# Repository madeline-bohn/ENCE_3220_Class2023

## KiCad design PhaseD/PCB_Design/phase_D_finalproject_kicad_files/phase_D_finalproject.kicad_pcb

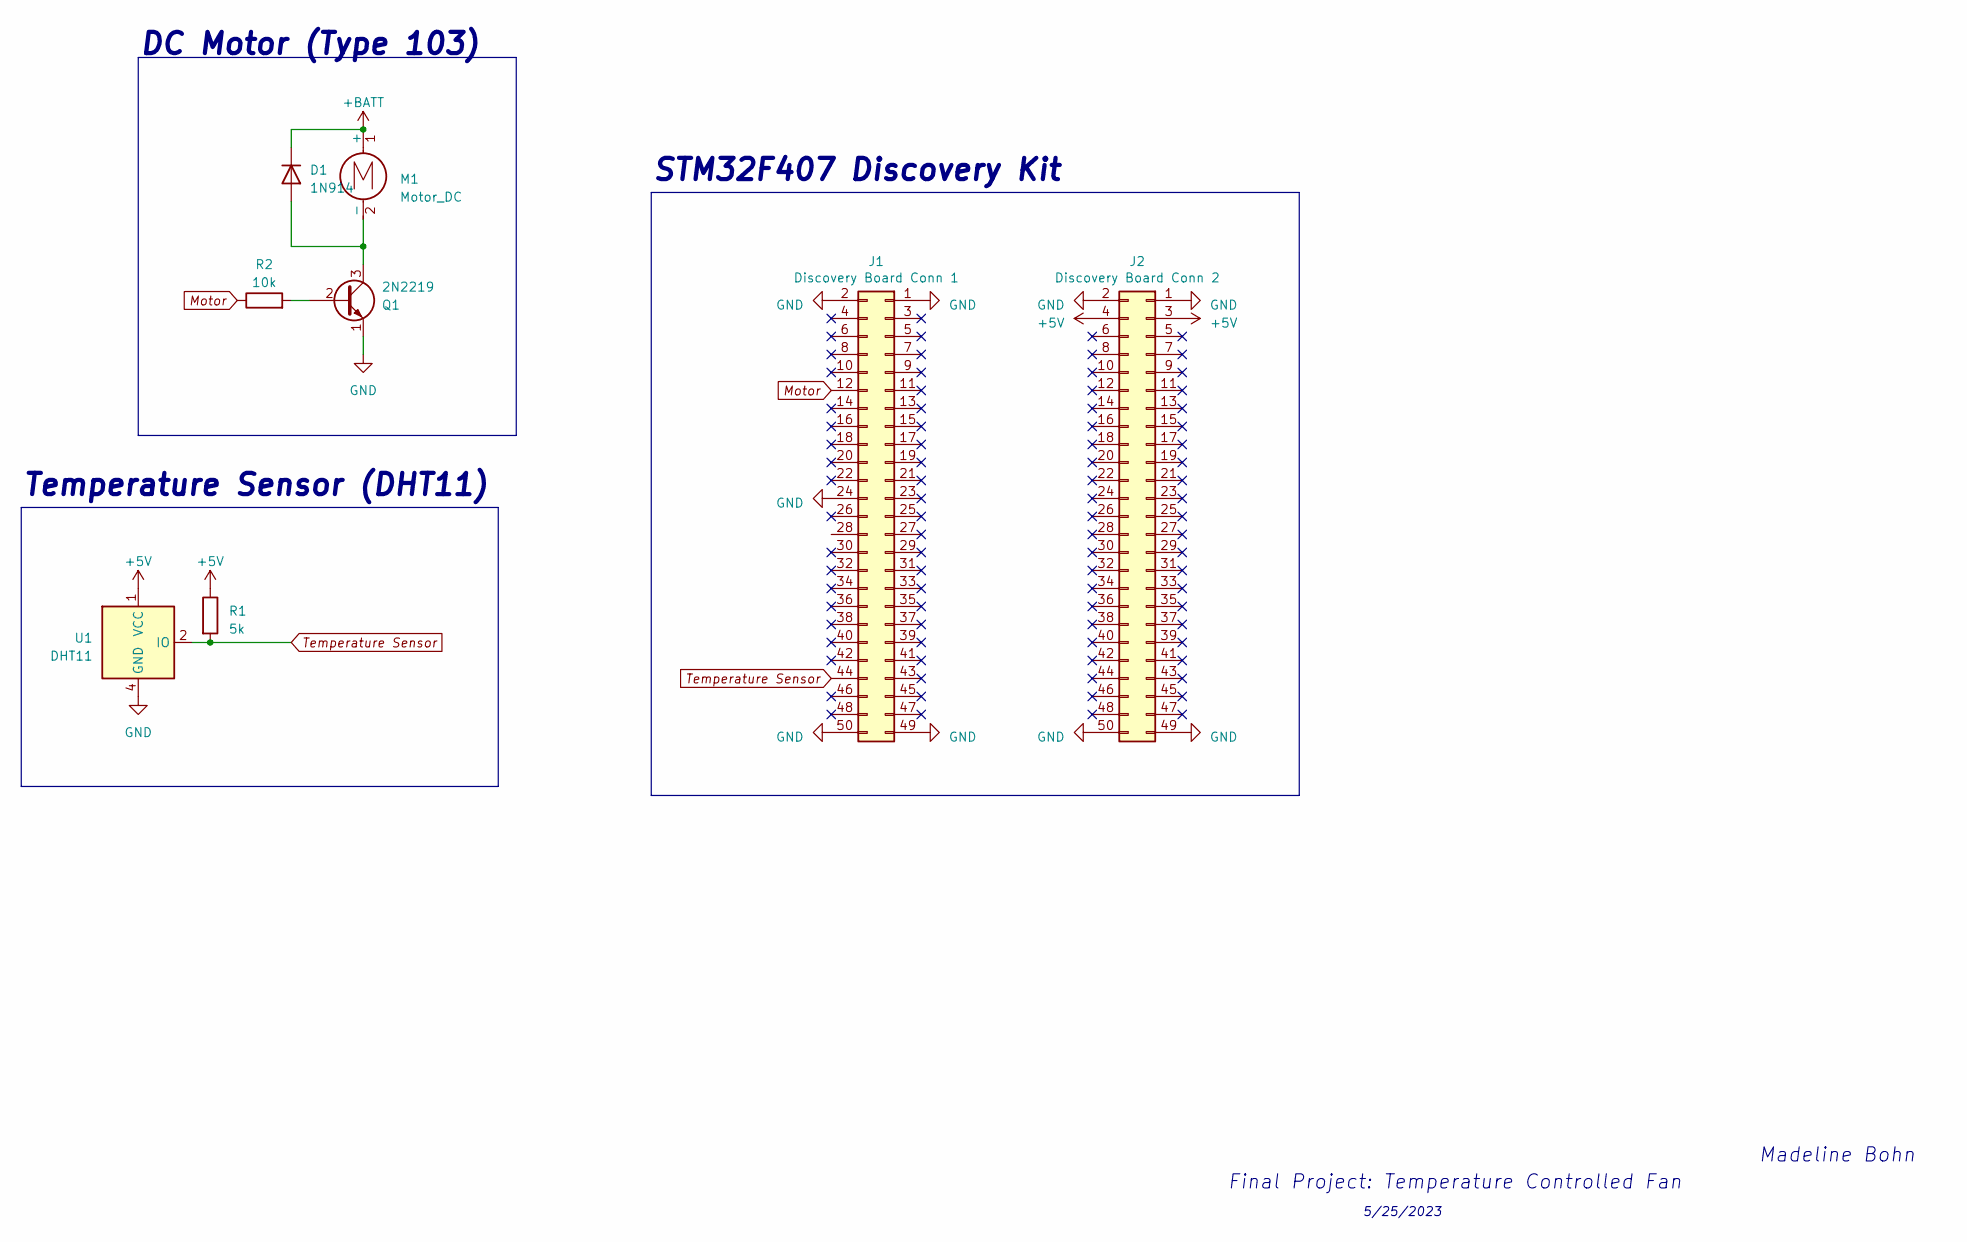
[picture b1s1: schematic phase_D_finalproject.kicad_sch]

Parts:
D1: 1N914; D_DO-35_SOD27_P7.62mm_Horizontal
J1: Discovery Board Conn 1; PinSocket_2x25_P2.54mm_Vertical
J2: Discovery Board Conn 2; PinSocket_2x25_P2.54mm_Vertical
M1: Motor_DC; Vybronics_VZ30C1T8219732L
Q1: 2N2219; TO-39-3
R1: 5k; R_Axial_DIN0204_L3.6mm_D1.6mm_P5.08mm_Vertical
R2: 10k; R_Axial_DIN0204_L3.6mm_D1.6mm_P5.08mm_Vertical
U1: DHT11; Aosong_DHT11_5.5x12.0_P2.54mm

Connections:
+5V: J2.3, J2.4, R1.1, U1.1 (VCC)
+BATT: D1.1 (K), M1.1 (+)
GND: J1.1, J1.2, J1.24, J1.49, J1.50, J2.1, J2.2, J2.49, J2.50, Q1.1 (E), U1.4 (GND)
Motor: J1.12, R2.1
unnamed: D1.2 (A), M1.2 (-), Q1.3 (C)
unnamed: Q1.2 (B), R2.2
Temperature Sensor: J1.44, R1.2, U1.2 (IO)

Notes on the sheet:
5/25/2023
STM32F407 Discovery Kit
Temperature Sensor (DHT11)
Madeline Bohn
DC Motor (Type 103)
Final Project: Temperature Controlled Fan

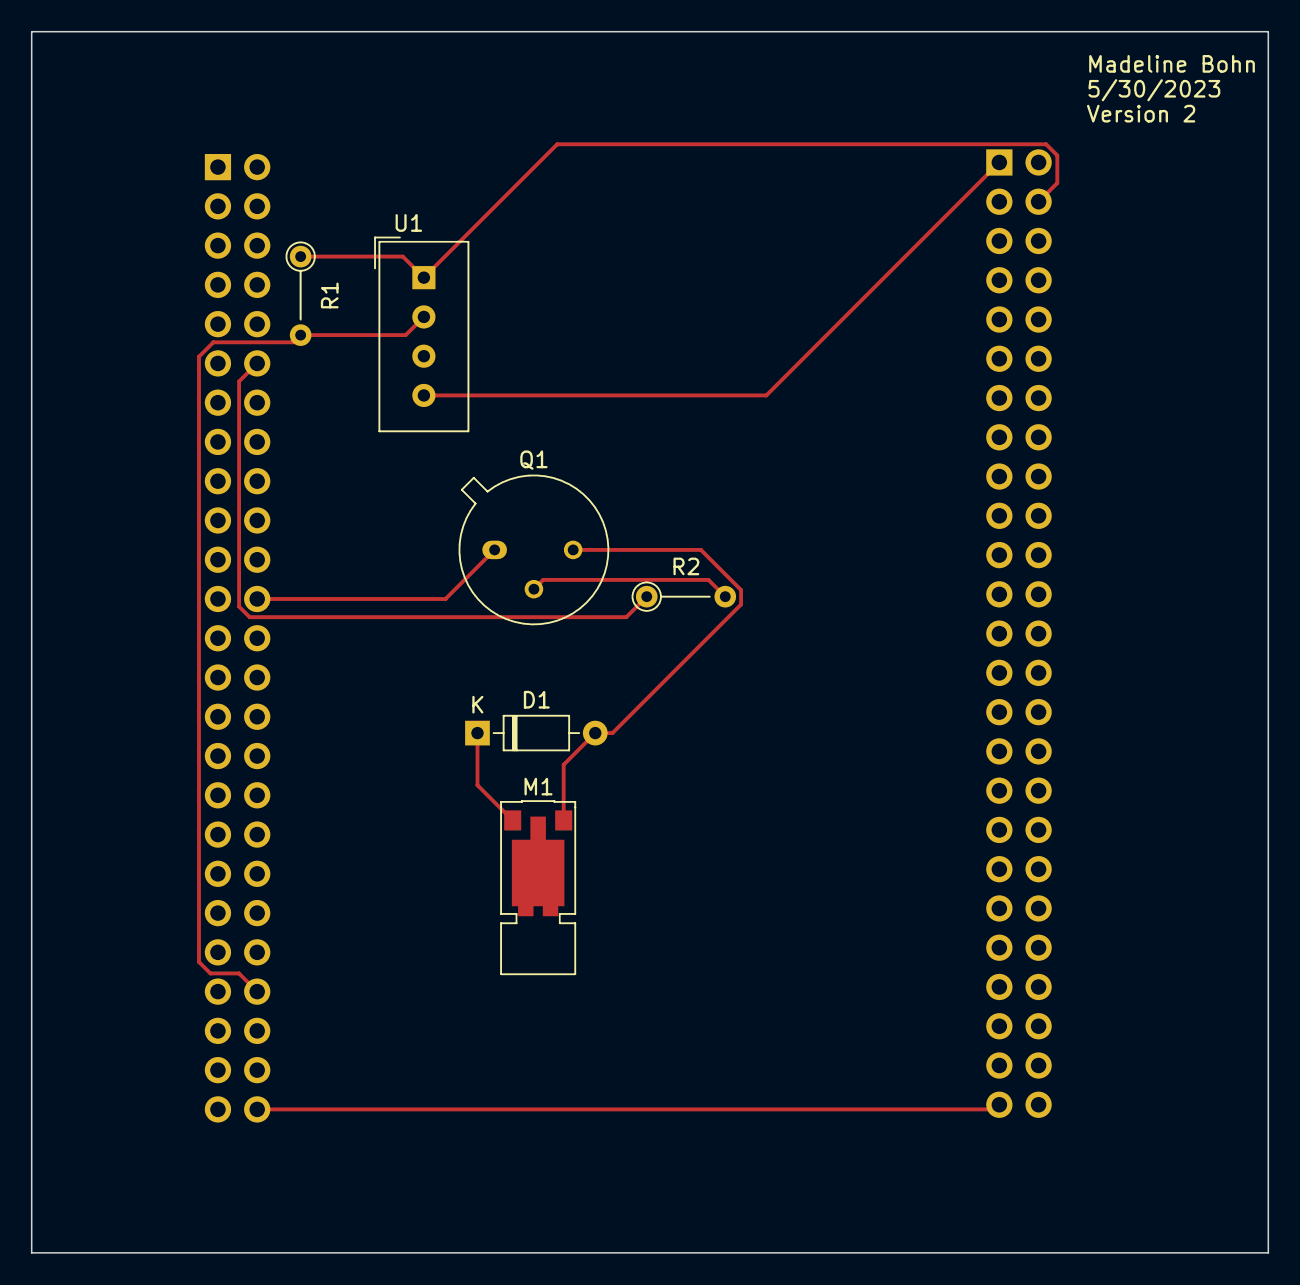
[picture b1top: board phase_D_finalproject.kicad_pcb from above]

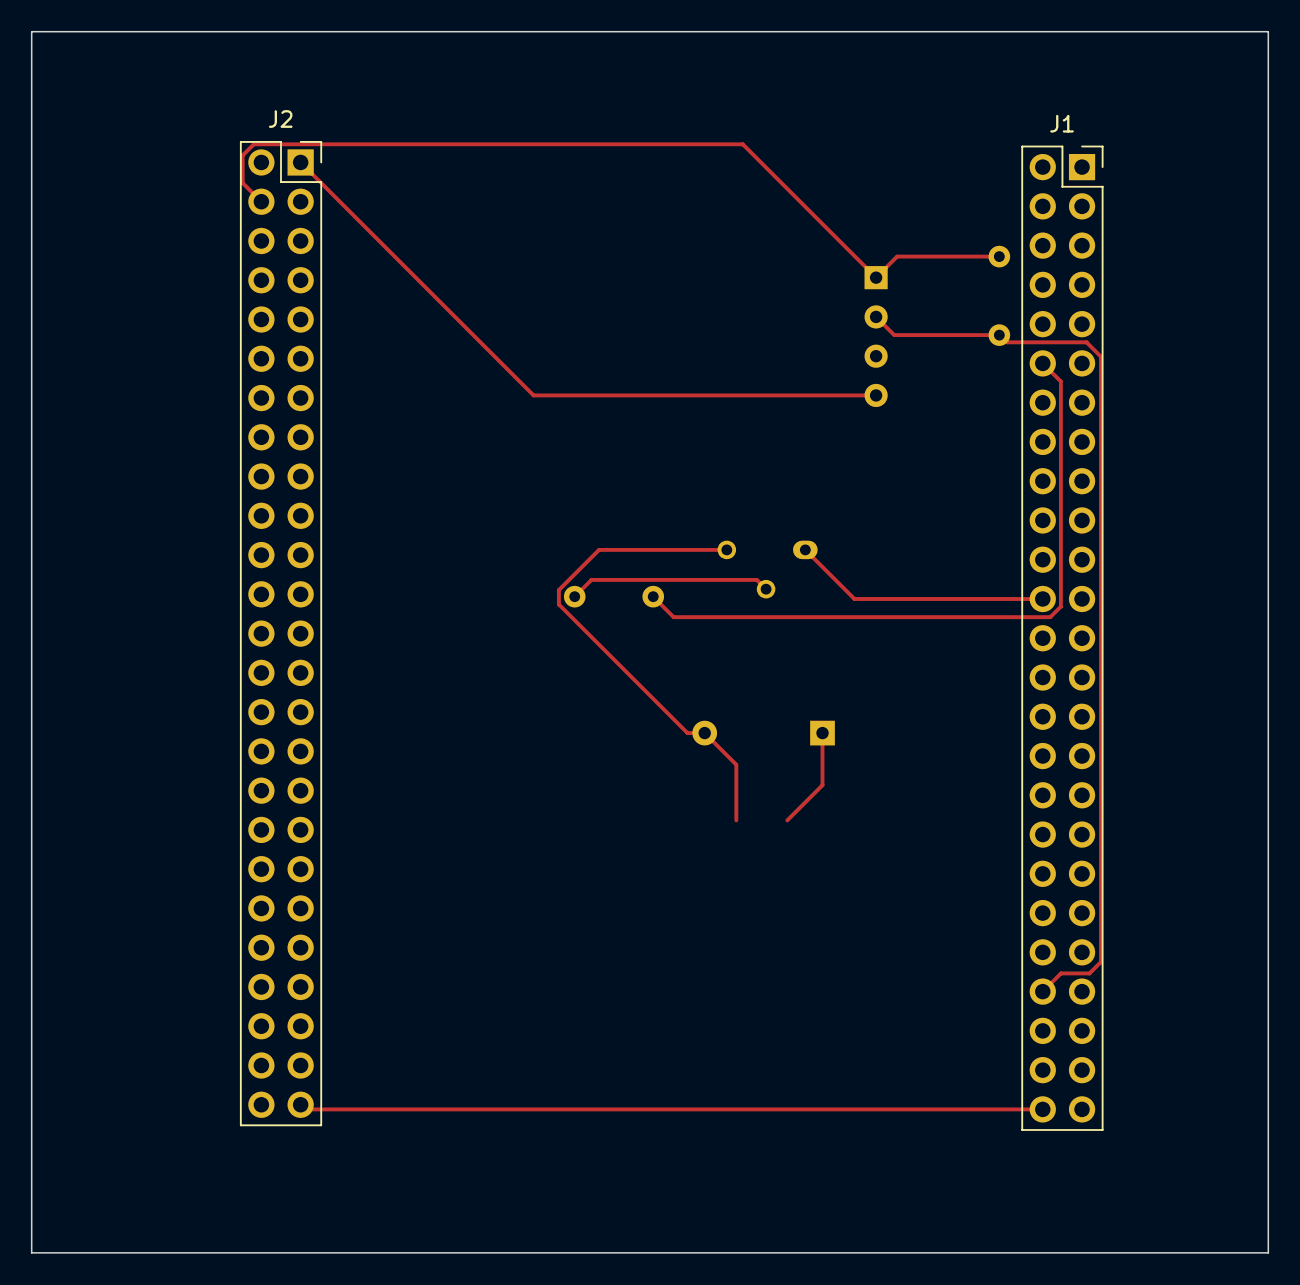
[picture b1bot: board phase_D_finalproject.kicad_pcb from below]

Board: 2 copper layers, 80.0 x 79.0 mm, 8 parts (2 on the bottom side), 7 nets.

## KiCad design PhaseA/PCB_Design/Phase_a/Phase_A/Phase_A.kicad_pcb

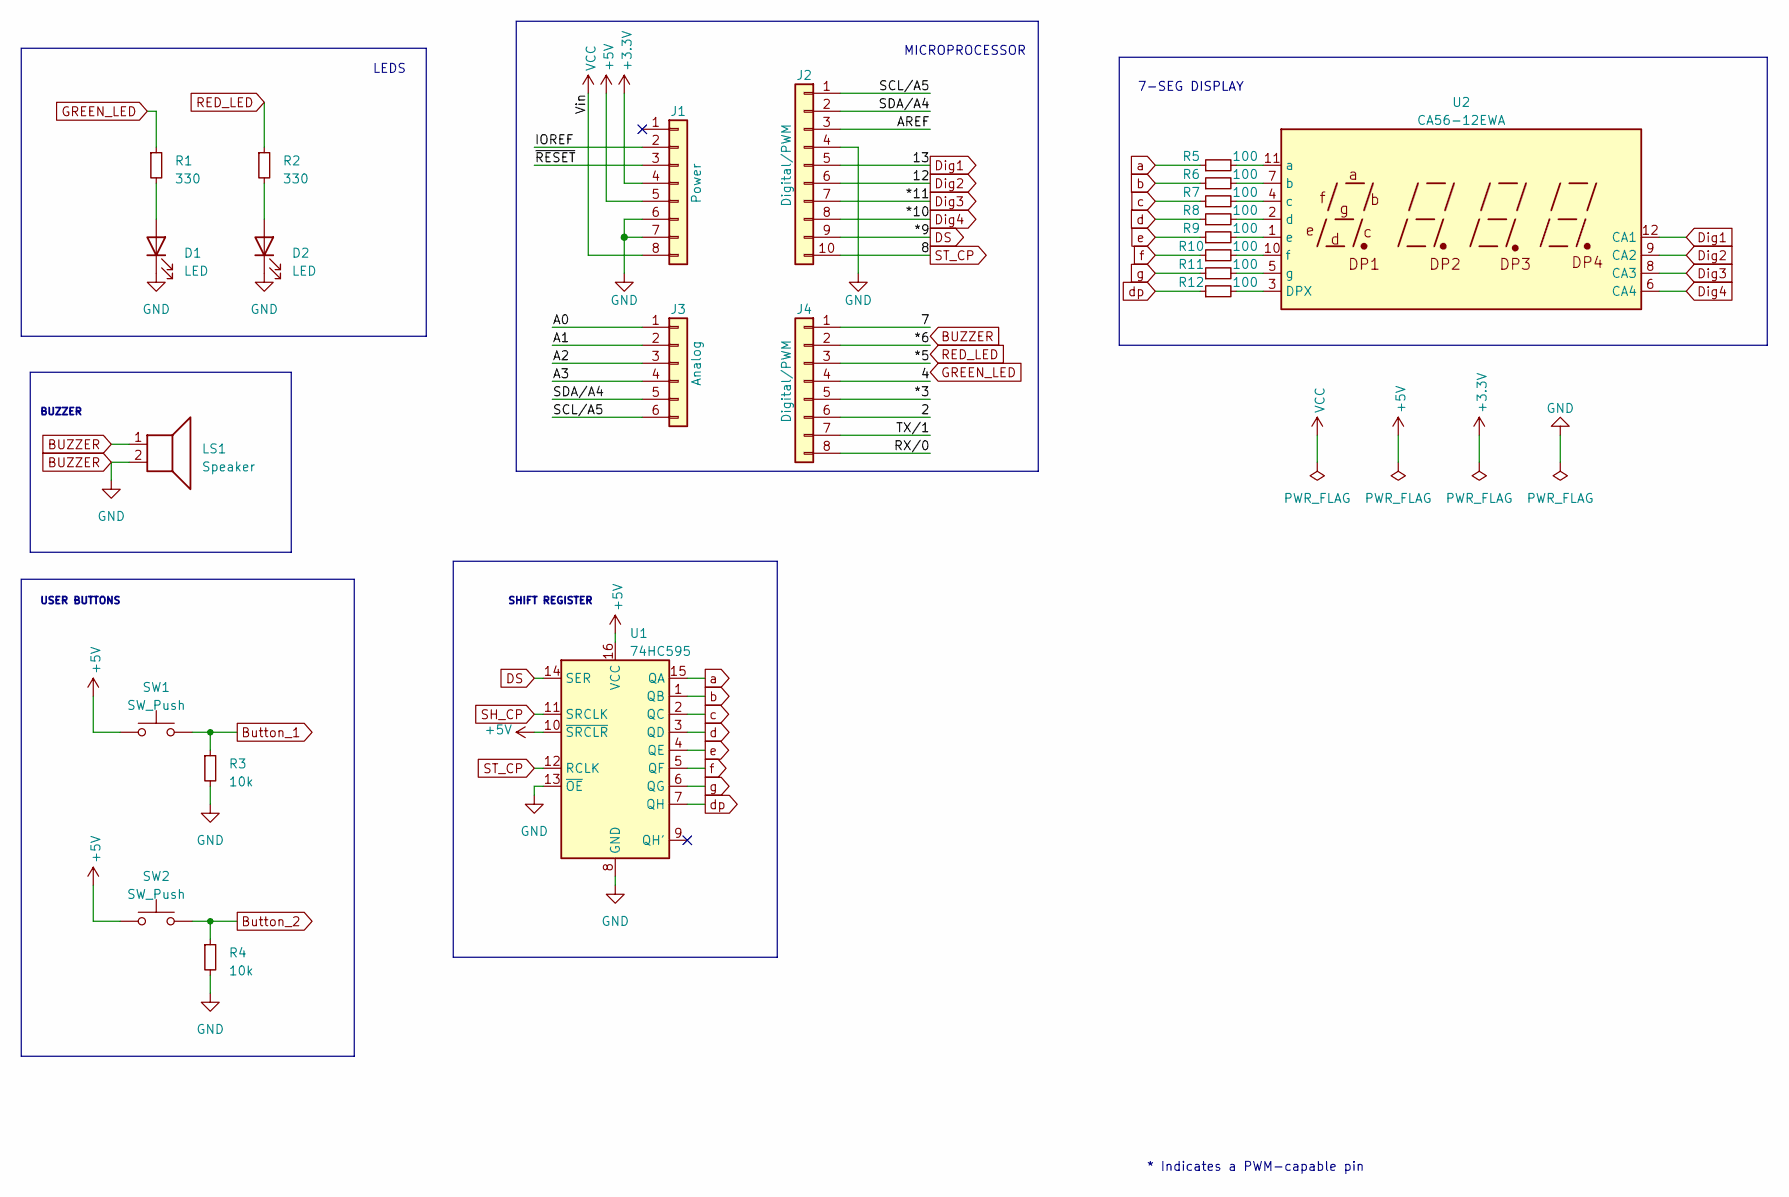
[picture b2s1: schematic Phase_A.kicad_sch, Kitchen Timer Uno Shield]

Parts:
D1, D2: LED; LED_D5.0mm
J1: Power; PinSocket_1x08_P2.54mm_Vertical
J2: Digital/PWM; PinSocket_1x10_P2.54mm_Vertical
J3: Analog; PinSocket_1x06_P2.54mm_Vertical
J4: Digital/PWM; PinSocket_1x08_P2.54mm_Vertical
LS1: Speaker; Buzzer_12x9.5RM7.6
R1, R2: 330; R_Axial_DIN0207_L6.3mm_D2.5mm_P10.16mm_Horizontal
R3, R4: 10k; R_Axial_DIN0207_L6.3mm_D2.5mm_P10.16mm_Horizontal
R5, R6, R7, R8, R9, R10, R11, R12: 100; R_Axial_DIN0207_L6.3mm_D2.5mm_P10.16mm_Horizontal
SW1, SW2: SW_Push; SW_PUSH-12mm
U1: 74HC595; DIP-16_W7.62mm_Socket_LongPads
U2: CA56-12EWA

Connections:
+3V3: J1.4
+5V: J1.5, SW1.1, SW2.1, U1.10 (~SRCLR), U1.16 (VCC)
/2: J4.6
/4: J4.4
/7: J4.1
/*3: J4.5
/*5: J4.3
/*6: J4.2
/A0: J3.1
/A1: J3.2
/A2: J3.3
/A3: J3.4
/AREF: J2.3
/IOREF: J1.2
/RX/0: J4.8
/SCL/A5: J2.1, J3.6
/SDA/A4: J2.2, J3.5
/TX/1: J4.7
/~RESET: J1.3
BUZZER: D1.1 (K), D2.1 (K), J1.6, J1.7, J2.4, LS1.1, LS1.2, R3.2, R4.2, U1.8 (GND), U1.13 (~OE)
Button_1: R3.1, SW1.2
Button_2: R4.1, SW2.2
DS: J2.9, U1.14 (SER)
Dig1: J2.5, U2.12 (CA1)
Dig2: J2.6, U2.9 (CA2)
Dig3: J2.7, U2.8 (CA3)
Dig4: J2.8, U2.6 (CA4)
GREEN_LED: R1.1
unnamed: D1.2 (A), R1.2
unnamed: D2.2 (A), R2.2
unnamed: R12.2, U2.3 (DPX)
unnamed: R5.2, U2.11 (a)
unnamed: R6.2, U2.7 (b)
unnamed: R7.2, U2.4 (c)
unnamed: R8.2, U2.2 (d)
unnamed: R9.2, U2.1 (e)
unnamed: R10.2, U2.10 (f)
unnamed: R11.2, U2.5 (g)
RED_LED: R2.1
SH_CP: U1.11 (SRCLK)
ST_CP: J2.10, U1.12 (RCLK)
VCC: J1.8
a: R5.1, U1.15 (QA)
b: R6.1, U1.1 (QB)
c: R7.1, U1.2 (QC)
d: R8.1, U1.3 (QD)
dp: R12.1, U1.7 (QH)
e: R9.1, U1.4 (QE)
f: R10.1, U1.5 (QF)
g: R11.1, U1.6 (QG)

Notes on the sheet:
MICROPROCESSOR
USER BUTTONS
* Indicates a PWM-capable pin
7-SEG DISPLAY
BUZZER
SHIFT REGISTER
LEDS

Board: 2 copper layers, 27 parts (0 on the bottom side), 30 nets, no tracks yet.

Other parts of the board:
MH1, MH2, MH3, MH4: MountingHole_3.2mm

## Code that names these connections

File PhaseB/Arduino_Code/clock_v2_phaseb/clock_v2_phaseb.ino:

#define BUTTON_2  2  
#define BUTTON_1  3  
#define GREEN_LED 4
#define RED_LED   5
#define BUZZER    6

#define DATA      9 // DS
#define LATCH     8 // ST_CP
#define CLOCK     7 // SH_CP

#define DIGIT_4   10
#define DIGIT_3   11
#define DIGIT_2   12
#define DIGIT_1   13

#define BUFF_SIZE 20

#define DEFAULT_COUNT 30 // default value is 30secs

// 7-Seg Display Variables
unsigned char gtable[]=
{0x3f,0x06,0x5b,0x4f,0x66,0x6d,0x7d,0x07,0x7f,0x6f,0x77,0x7c
,0x39,0x5e,0x79,0x71,0x00};
byte gCurrentDigit;

// Volatile Variables
volatile unsigned char gISRFlag1 = 0;
volatile unsigned char gBuzzerFlag = 0;
volatile unsigned char gISRFlag2 = 0;
volatile unsigned char gbuttonISR1 = 0;
volatile unsigned char gbuttonISR2 = 0;
volatile int  gCount = DEFAULT_COUNT;

// Timer Variables
unsigned char gTimerRunning = 0; 
unsigned int gReloadTimer1 = 62500; // corresponds to 1 second
unsigned int gReloadTimer2 = 100;
byte gReloadTimerDisplay = 10;  // display refresh time
char gIncomingChar;
char gCommMsg[BUFF_SIZE];
int buff = 0;
byte gPackageFlag = 0;
byte gProcessFlag = 0;


void setup() {
   // LEDs Pins
  pinMode(RED_LED, OUTPUT);
  pinMode(GREEN_LED, OUTPUT);

  // LEDs -> Timer Stopped
  digitalWrite(RED_LED, HIGH);
  digitalWrite(GREEN_LED, HIGH);

  // Button Pins
  pinMode(BUTTON_1, INPUT_PULLUP);
  attachInterrupt(digitalPinToInterrupt(BUTTON_1), gbuttonISR1, RISING);
  pinMode(BUTTON_2, INPUT_PULLUP);
  attachInterrupt(digitalPinToInterrupt(BUTTON_2), gbuttonISR2, RISING);

  // Buzer Pins
  pinMode(BUZZER, OUTPUT);

  // Buzzer -> Off
  digitalWrite(BUZZER,LOW);

  // 7-Seg Display
  pinMode(DIGIT_1, OUTPUT);
  pinMode(DIGIT_2, OUTPUT);
  pinMode(DIGIT_3, OUTPUT);
  pinMode(DIGIT_4, OUTPUT);

  // Shift Register Pins
  pinMode(LATCH, OUTPUT);
  pinMode(CLOCK, OUTPUT);
  pinMode(DATA, OUTPUT);

  dispOff();  // turn off the display
  pinMode(LED, OUTPUT); //declare led as an output
  Serial.begin(9600); //baud rate of 9600

  // Initialize Timer1
  // Speed of Timer1 = 16MHz/64 = 250 KHz
  TCCR1A = 0;
  TCCR1B = 0;
  OCR1A = gReloadTimer1;            // max value 2^16 - 1 = 65535
  TCCR1A |= (1<<WGM11);
  TCCR1B = (1<<CS11) | (1<<CS10);   // 64 prescaler
  TIMSK1 |= (1<<OCIE1A);
  interrupts(); 
}
void display(unsigned char num, unsigned char dp){
  digitalWrite(LATCH, LOW);
  shiftOut(DATA, CLOCK, MSBFIRST, gtable[num] | (dp<<7));
  digitalWrite(LATCH, HIGH);
}
//used to compare two arrays of chars to see if equal
char compareMsg(char a[], char b[], int size){
  int i; 
  char result;

  for(i = 0;  i < size; i++){
    if(a[i] != b[i]){
      result = 0; //arrays not equal
    }else{
      result = 1; //arrays are equal
    }
  } 
  return result;
} 
//interrupt routine to read data from ESP
ISR(TIMER_COMPA_vect){ 
  if(Serial.available()>0){
    gISRFlag2 = 1;
  }
}
void dispOff(){
   digitalWrite(DIGIT_1, HIGH);
   digitalWrite(DIGIT_2, HIGH);
   digitalWrite(DIGIT_3, HIGH);
   digitalWrite(DIGIT_4, HIGH);
}
void buttonISR2(){
  //increment clock
  gCount++;
}
void buttonISR1(){ 
  // Set ISR Flag
  gISRFlag1 = 1;
}

// Timer2 interrupt service routine (ISR)
ISR(TIMER2_COMPA_vect) {
  dispOff();  // turn off the display
  OCR2A = gReloadTimer2;  // load timer
 
  switch (gCurrentDigit) {
    case 1: //0x:xx
      display( int((gCount/60) / 10) % 6, 0 );   // prepare to display digit 1 (most left)
      digitalWrite(DIGIT_1, LOW);  // turn on digit 1
      break;
 
    case 2: //x0:xx
      display( int(gCount / 60) % 10, 1 );   // prepare to display digit 2
      digitalWrite(DIGIT_2, LOW);     // turn on digit 2
      break;
 
    case 3: //xx:0x
      display( (gCount / 10) % 6, 0 );   // prepare to display digit 3
      digitalWrite(DIGIT_3, LOW);    // turn on digit 3
      break;
 
    case 4: //xx:x0
      display(gCount % 10, 0); // prepare to display digit 4 (most right)
      digitalWrite(DIGIT_4, LOW);  // turn on digit 4
      break;

    default:
      break;
  }
  gCurrentDigit = (gCurrentDigit % 4) + 1;
}

// Timer1 interrupt service routine (ISR)
ISR(TIMER1_COMPA_vect){
  gCount--;
  OCR1A = gReloadTimer1;

  if(gCount == 0) {
      // Stop Timer
      stopTimer1();
      
      // Raise Alarm
      gBuzzerFlag = 1;
      gTimerRunning = 0;
  }
}
void stopTimer1(){
  // Stop Timer
  TCCR1B = 0; // stop clock
  TIMSK1 = 0; // cancel clock timer interrupt
}
void startTimer1(){
  // Initialize Timer1 (16bit) -> Used for clock
  // Speed of Timer1 = 16MHz/256 = 62.5 KHz
  noInterrupts();
  TCCR1A = 0;
  TCCR1B = 0;
  OCR1A = gReloadTimer1; // compare match register 16MHz/256
  TCCR1B |= (1<<WGM12);   // CTC mode
  TCCR1B |= (1<<CS12);    // 256 prescaler 
  TIMSK1 |= (1<<OCIE1A);  // enable timer compare interrupt
  interrupts();
}
void activeBuzzer(){
  unsigned char i;
  unsigned char sleepTime = 1; // ms
  
  for(i=0;i<100;i++){
    digitalWrite(BUZZER,HIGH);
    delay(sleepTime);//wait for 1ms
    digitalWrite(BUZZER,LOW);
    delay(sleepTime);//wait for 1ms
  }
}
void loop() {
  char messageBuff[BUFF_SIZE];
  int auxCount = 0;
  unsigned char auxDigit = '0';


  if(gISRFlag1 == 1 || gISRFlag2 == 1){
    // Reset ISR Flag
    gISRFlag1 = 0;
    gISRFlag2 = 0;

    gIncomingChar = Serial.read(); //read incoming data

    if(gPackageFlag == 1){
      gCommMsg[buff] = gIncomingChar;  //if new message add to buffer and increment size
      buff++; 

      if(buff == BUFF_SIZE){
        gPackageFlag = 0; //if at max size reset start flag and raise processor flag
        gProcessFlag = 1;
      }
    }
    if(gIncomingChar == '$'){
      gPackageFlag = 1; //if start of msg -> raise flag

      int i;
      for(int i = 0; i<BUFF_SIZE; i++){
        gCommMsg[i] == 0; //set message to 0
      }
      buff = 0; //set msg index to 0
    }

    if((gIncomingChar == '\n') && (gPackageFlag == 1)){
      gPackageFlag = 0; //signal end of msg
      gProcessFlag == 1;
    }
    if(gTimerRunning == 0){
      // Start Timer
      gTimerRunning = 1;

      if(gCount == 0){
        gCount = DEFAULT_COUNT;
      }      
      if(gBuzzerFlag == 1){
        gBuzzerFlag = 0;

        // LEDs -> Timer Stopped
        digitalWrite(RED_LED, HIGH);
        digitalWrite(GREEN_LED, HIGH);
      }
      else
      {
        startTimer1();
        // LEDs -> Timer Running
        digitalWrite(RED_LED, LOW);
        digitalWrite(GREEN_LED, HIGH);
      }
    }
    else
    {
      // Stop Timer
      stopTimer1();
      gTimerRunning = 0;

      // LEDs -> Timer Running
      digitalWrite(RED_LED, HIGH);
      digitalWrite(GREEN_LED, HIGH);
    }
  }
  if(gProcessFlag == 1){
      gProcessFlag = 0; //reset flag

      if(compareMsg(gCommMsg, "STR", 3) == 1){
        digitalWrite(GREEN_LED, HIGH); //if start signal -> turn LED on
      }
      if(compareMsg(gCommMsg, "STP",3) == 1){
        digitalWrite(RED_LED, LOW); //if stop signal -> turn LED off
      }
      if(compareMsg(gCommMsg, "GET", 3) == 1){
        Serial.print("$00:01\n"); //if get signal -> send clock status
      }
    }


  // Attend gBuzzerFlag
  if(gBuzzerFlag == 1){
    // Make Noise...
    digitalWrite(RED_LED, HIGH);
    digitalWrite(GREEN_LED, LOW);
    activeBuzzer();
  }
}

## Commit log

2023-04-13 arduino and kicad files for phase a
2023-04-13 notes
2023-04-21 PhaseB
2023-05-04 code
2023-05-04 report
2023-06-01 phaseD
